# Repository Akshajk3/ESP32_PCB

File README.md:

# ESP32_PCB
A simple PCB made using a ESP32 to learn microcontroller design.

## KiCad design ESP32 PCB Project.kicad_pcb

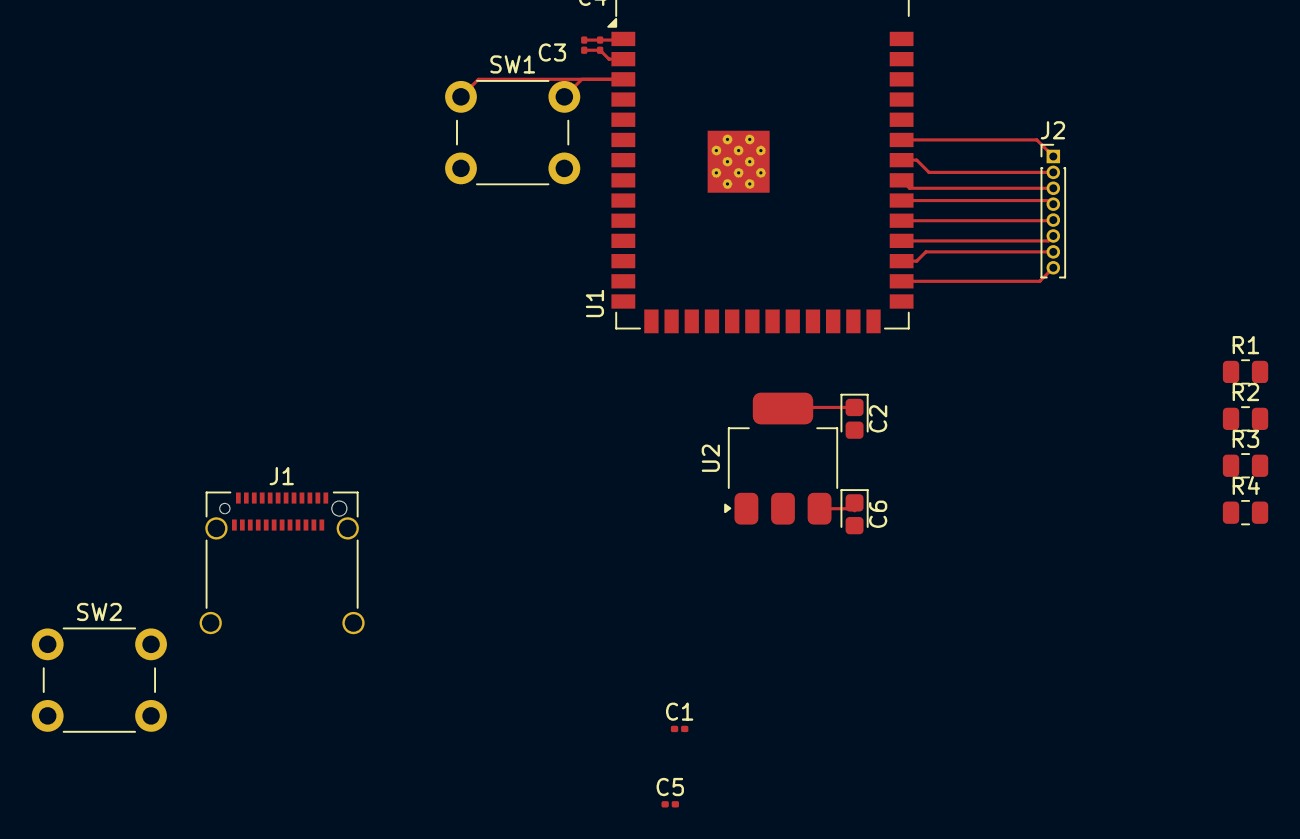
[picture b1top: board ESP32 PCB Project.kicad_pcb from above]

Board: 2 copper layers, 16 parts (0 on the bottom side), 17 nets.

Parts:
C1: 100nf; C_0201_0603Metric
C2: 22uf; CP_EIA-1608-08_AVX-J
C3: 22uF; C_0201_0603Metric
C4, C5: 0.1uF; C_0201_0603Metric
C6: 10uf; CP_EIA-1608-08_AVX-J
J1: USB_C_Receptacle_USB2.0_16P; USB_C_Receptacle_Amphenol_12401610E4-2A_CircularHoles
J2: Conn_01x08_Pin; PinHeader_1x08_P1.00mm_Vertical
R1: 10k; R_0805_2012Metric
R2: 100R; R_0805_2012Metric
R3, R4: 5.1K; R_0805_2012Metric
SW1, SW2: SW_Push; SW_PUSH_6mm
U1: ESP32-S3-WROOM-1
U2: AMS1117-3.3; SOT-223-3_TabPin2

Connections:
+3V3: C2.1, C3.2, C4.1, R1.1, U1.2 (3V3), U2.2 (VO)
+5V: C6.1, J1.A4 (VBUS), J1.A9 (VBUS), J1.B4 (VBUS), J1.B9 (VBUS), U2.3 (VI)
D+: J1.A6 (D+), J1.B6 (D+), U1.14 (USB_D+)
D-: J1.A7 (D-), J1.B7 (D-), U1.13 (USB_D-)
Enable: C1.1, C5.1, R1.2, SW1.1, U1.3 (EN)
GND: C1.2, C2.2, C3.1, C4.2, C5.2, C6.2, J1.A1 (GND), J1.A12 (GND), J1.B1 (GND), J1.B12 (GND), J1.S1 (SHIELD), R3.2, R4.2, SW1.2, SW2.2, U1.1 (GND), U1.40 (GND), U1.41 (GND)
unnamed: J1.A5 (CC1), R3.1
unnamed: J1.B5 (CC2), R4.1
unnamed: J2.1, U1.35 (IO42)
unnamed: J2.2, U1.34 (IO41)
unnamed: J2.3, U1.33 (IO40)
unnamed: J2.4, U1.32 (IO39)
unnamed: J2.5, U1.31 (IO38)
unnamed: J2.6, U1.30 (IO37)
unnamed: J2.7, U1.29 (IO36)
unnamed: J2.8, U1.28 (IO35)
unnamed: R2.2, SW2.1

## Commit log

2025-11-13 finished schematic and started layout
2025-11-19 began the pcb layout
